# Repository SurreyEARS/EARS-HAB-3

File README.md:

# EARS-HAB-3

This repository contains the hardware and software for the HAB-3 board. This board is based on the STM32F3303VC, a microcontroller from ST Microelectronics based on the Cortex-M4.

This project's goal is to provide experience working with bare metal microcontrollers. Also ideally a working flight computer!

You can find more information on the wiki: http://wiki.surreyears.co.uk/index.php/HAB-3
And discussion on the forums: http://forum.surreyears.co.uk/topic/36/hab-3

The toolchain for this project is the free version of Atollic TrueSTUDIO for ARM (http://timor.atollic.com/truestudio/), backed up by arm-atollic-eabi-gcc (same installer).

We have two STM32F3 DISCOVERY development boards for working on this; one is currently with Revanth and the other is with James.

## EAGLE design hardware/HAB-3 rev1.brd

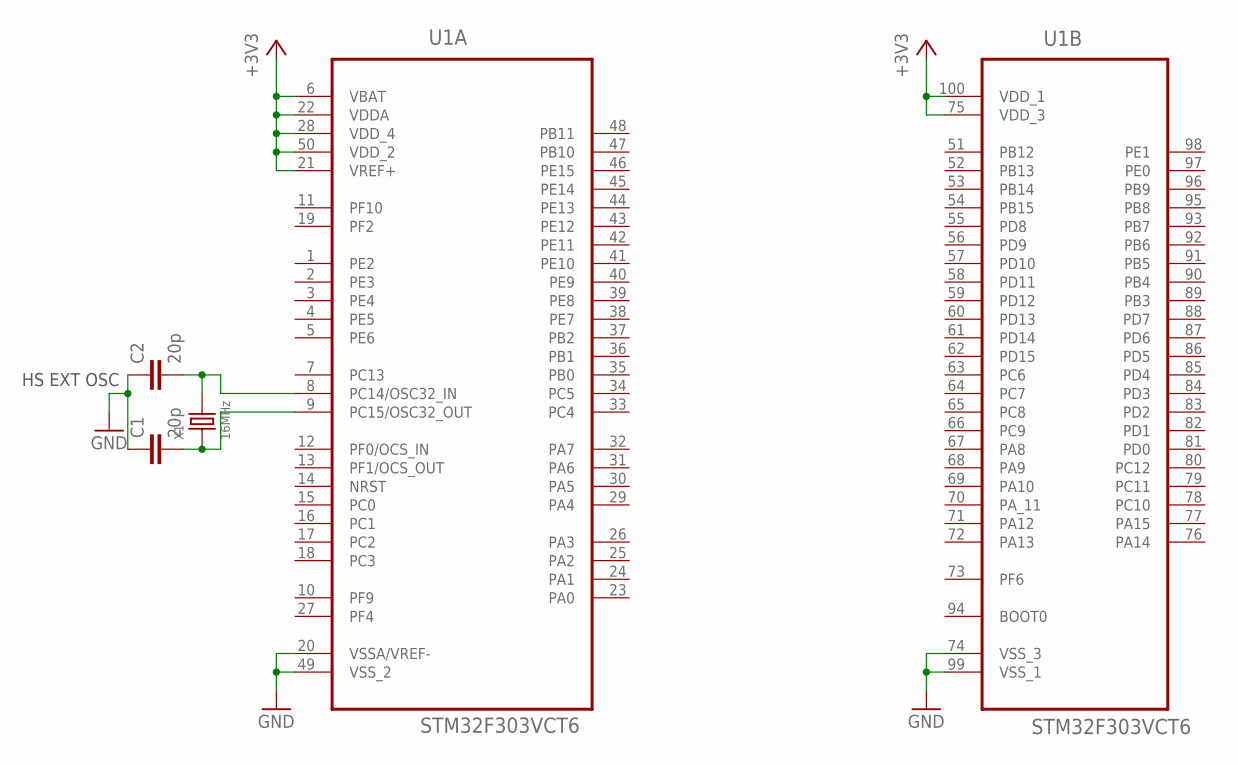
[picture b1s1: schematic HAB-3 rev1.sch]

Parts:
C1, C2: 20p; C0603
U1: STM32F303VCT6; QFP50P1600X1600X160-100N
X1: 16MHz; X4-SMD-3.2X2.5X0.7MM

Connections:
+3V3: U1.6 (VBAT), U1.21 (VREF+), U1.22 (VDDA), U1.28 (VDD_4), U1.50 (VDD_2), U1.75 (VDD_3), U1.100 (VDD_1)
GND: C1.1, C2.1, U1.20 (VSSA/VREF-), U1.49 (VSS_2), U1.74 (VSS_3), U1.99 (VSS_1)
unnamed: C2.2, U1.8 (PC14/OSC32_IN), X1.3 (2)
unnamed: C1.2, U1.9 (PC15/OSC32_OUT), X1.1
PF2: U1.19 (PF2)

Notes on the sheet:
HS EXT OSC

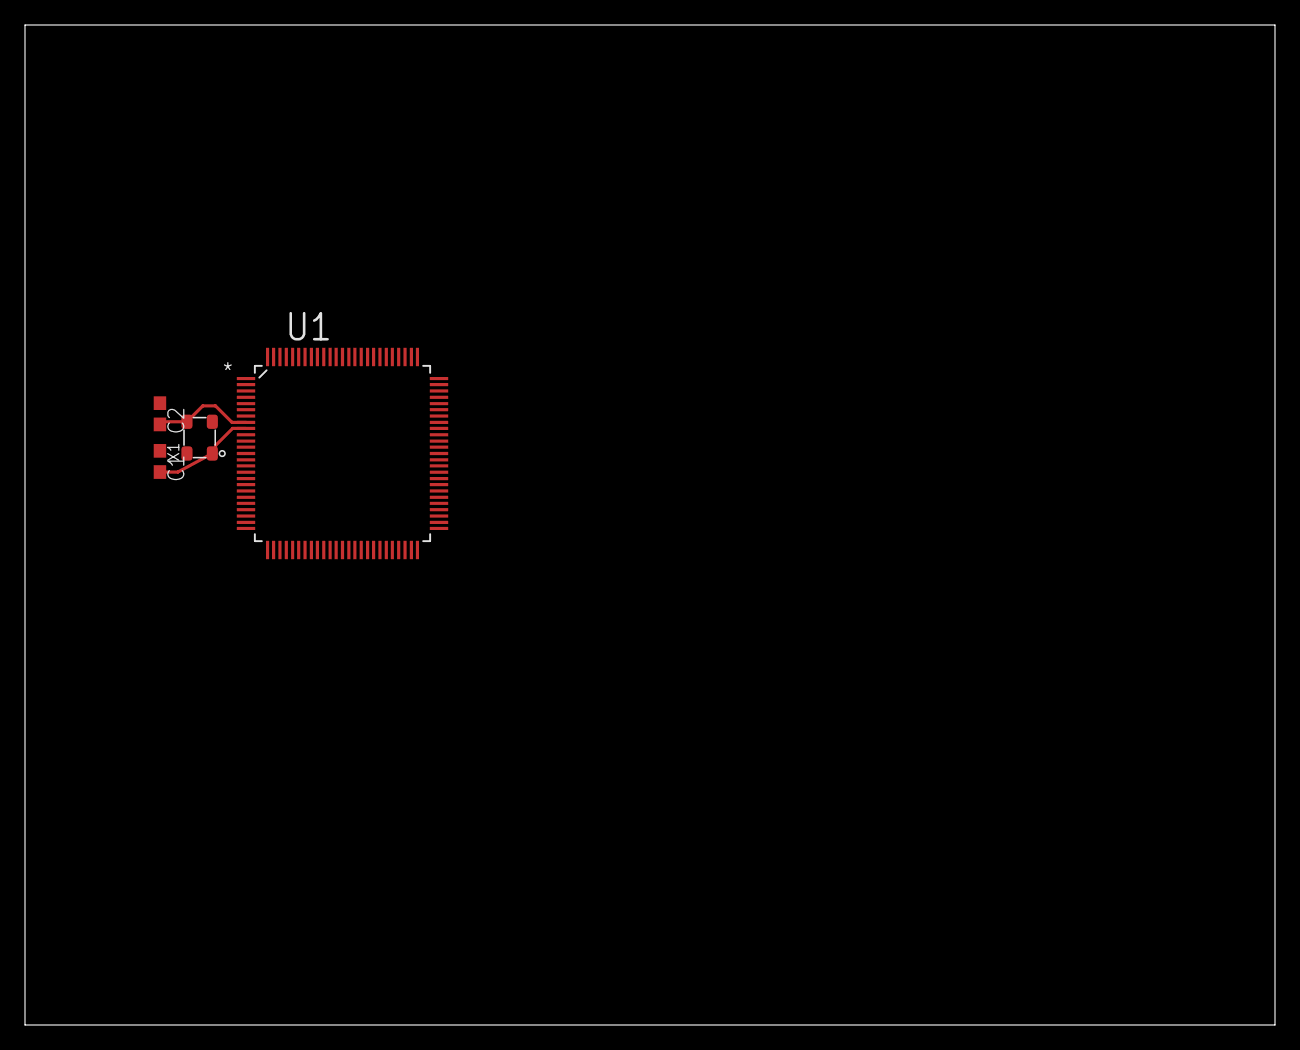
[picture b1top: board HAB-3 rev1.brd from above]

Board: 2 copper layers, 100.0 x 80.0 mm, 4 parts (0 on the bottom side), 4 nets.

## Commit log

2015-11-21 Initial commit. Contains a bunch of drivers we don't need, which I am working on removing.
2015-11-21 Renamed the apl/asl/ext/hal/mal folders so that #includes are case insensitive on unix.
2015-11-21 Added a board that contains the processor and a crystal. More or less a placeholder.
2015-11-22 Removed all drivers as promised. This project is now officially 100% written by James!
2015-11-26 Added DAC module. It even works! It needs a timer module before DMA can be properly triggered though.
    Adjusted the way DMA works and hid the channel details from the
    implementer.
2016-01-01 Oops. Lots of code! I will commit more frequently from now on.
    Adjusted MAL organisation. Added standard way for a module to be
    configured [void configure (const InitStruct& config)] and tested [bool
    test()]. Tests run in main if a particular GPIO pin is pulled low, but
    can be overriden (if there is a fast-start requirement) by pulling that
    pin high.
    Many modules are still heavily WIP.
